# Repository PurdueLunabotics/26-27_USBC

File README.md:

# USBC board

Makes a stable USB-C voltage signal out of a DC input.

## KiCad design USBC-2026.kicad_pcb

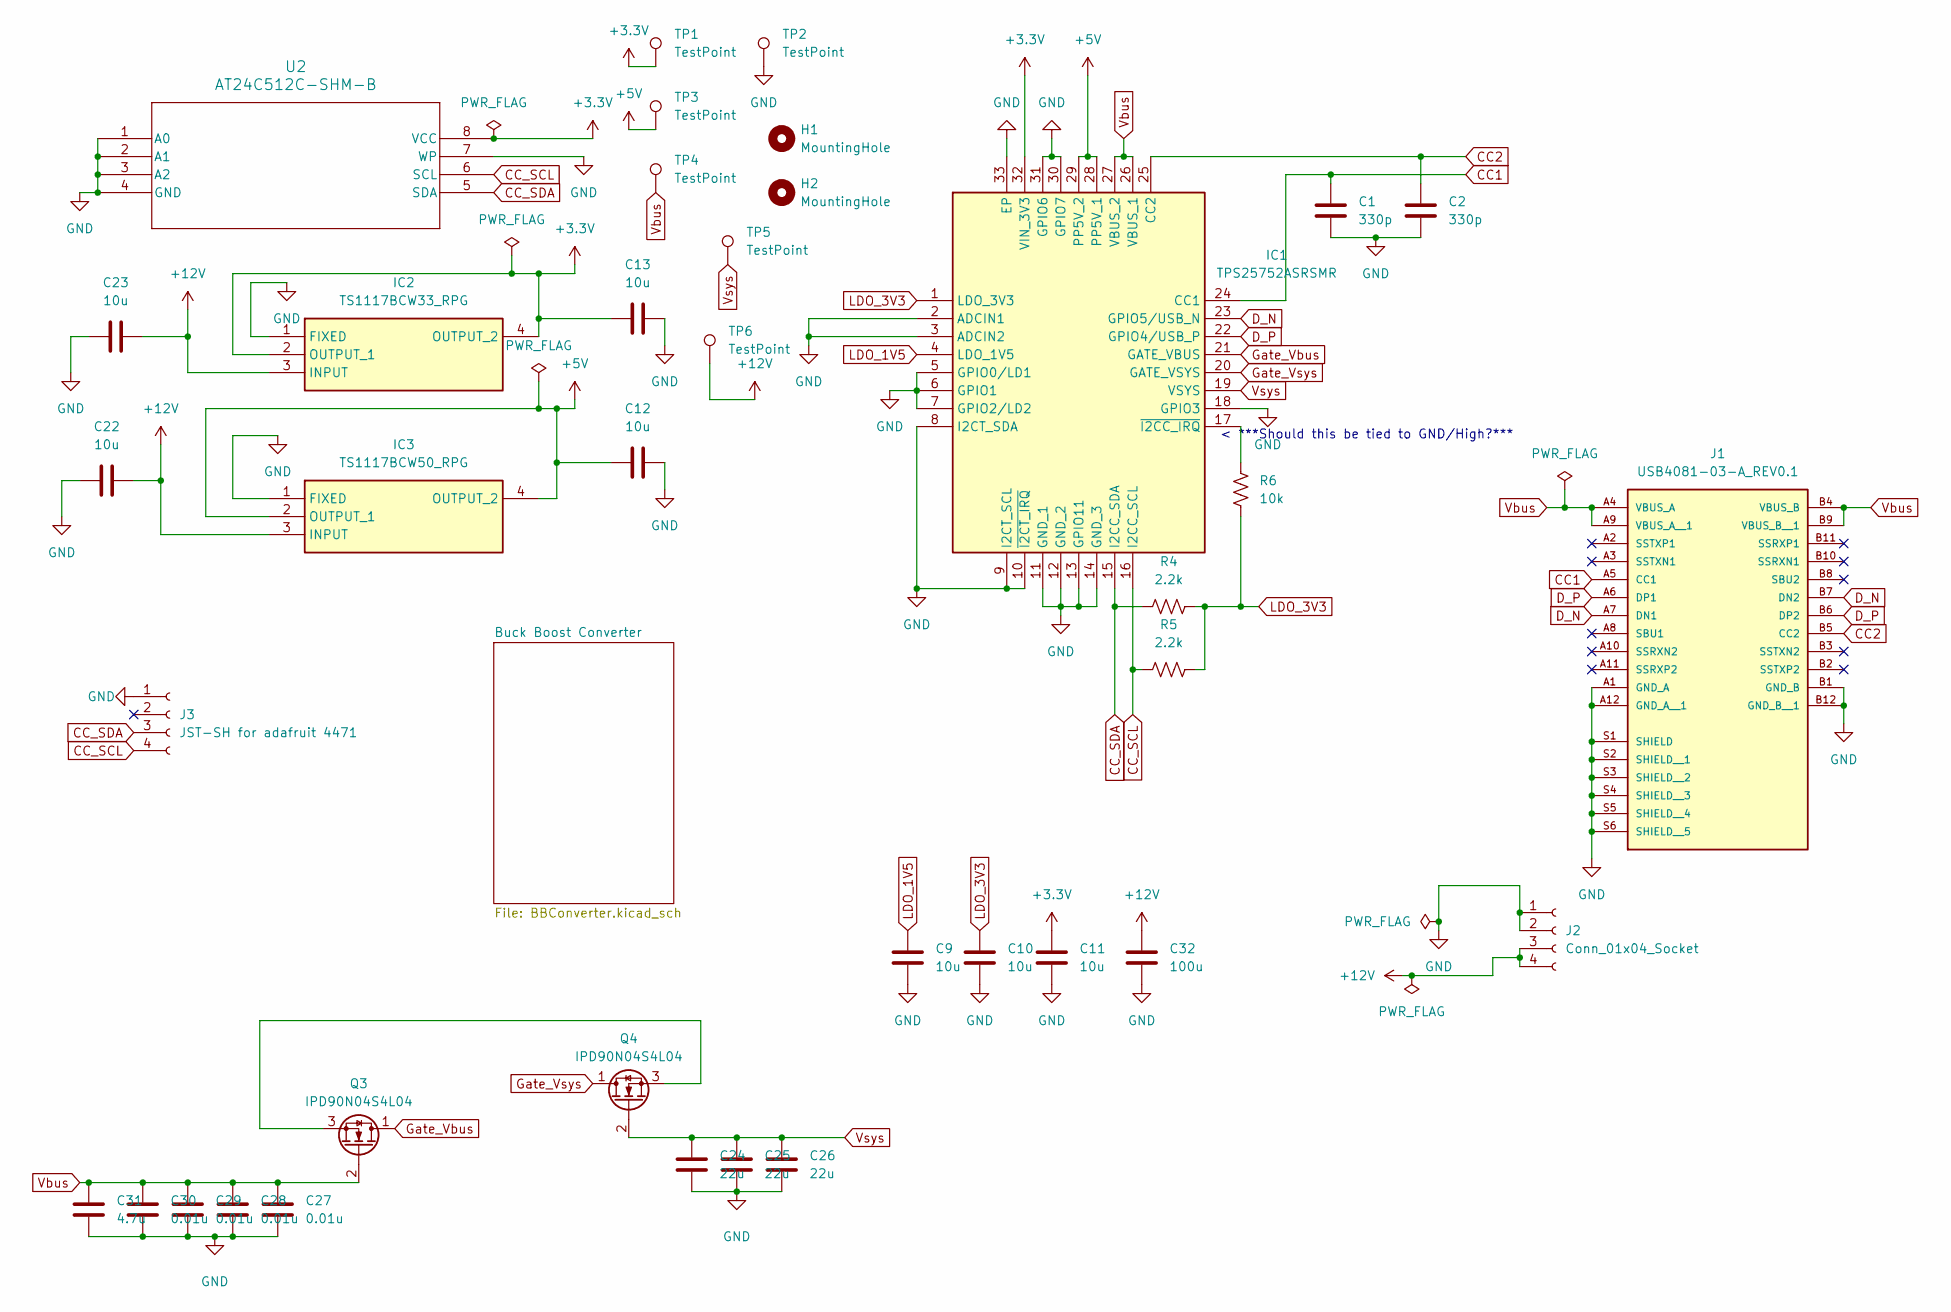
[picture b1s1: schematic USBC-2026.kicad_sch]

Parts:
C1, C2: 330p; C_0402_1005Metric
C9, C10, C11, C12, C13, C22, C23: 10u; C_0603_1608Metric
C24, C25, C26: 22u; C_1210_3225Metric
C27, C28, C29, C30: 0.01u; C_0402_1005Metric
C31: 4.7u; C_0603_1608Metric
C32: 100u; CP_Radial_D8.0mm_P3.50mm
H1, H2: MountingHole; MountingHole_2.2mm_M2_DIN965_Pad_TopBottom
IC1: TPS25752ASRSMR; QFN40P400X400X100-33N-D; Manufacturer_Part_Number TPS25752ASRSMR
IC2: TS1117BCW33_RPG; SOT-223; Mouser Part Number 821-TS1117BCW33RPG
IC3: TS1117BCW50_RPG; SOT-223; Mouser Part Number 821-TS1117BCW50RPG
J1: USB4081-03-A_REV0.1; GCT_USB4081-03-A_REV0.1; MPN USB4081-03-A
J2: Conn_01x04_Socket; CONN2_2604-1102_WAG
J3: JST-SH for adafruit 4471; JST_SH_BM04B-SRSS-TB_1x04-1MP_P1.00mm_Vertical
Q3, Q4: IPD90N04S4L04; TO-252-2
R4, R5: 2.2k; R_0402_1005Metric
R6: 10k; R_0402_1005Metric
TP1, TP2, TP3, TP4, TP5, TP6: TestPoint; TestPoint_Pad_D1.0mm
U2: AT24C512C-SHM-B; SOIC-8_3.9x4.9mm_P1.27mm

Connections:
+3.3V: C11.1, C13.1, IC1.32 (VIN_3V3), IC2.2 (OUTPUT_1), IC2.4 (OUTPUT_2), TP1.1 (1_1), U2.8 (VCC)
+5V: C12.1, IC1.28 (PP5V_1), IC1.29 (PP5V_2), IC3.2 (OUTPUT_1), IC3.4 (OUTPUT_2), TP3.1 (1_1)
+12V: C22.2, C23.2, C32.1, IC2.3 (INPUT), IC3.3 (INPUT), J2.3, J2.4, TP6.1 (1_1); also elsewhere on the board
CC1: C1.1, IC1.24 (CC1), J1.A5 (CC1)
CC2: C2.1, IC1.25 (CC2), J1.B5 (CC2)
CC_SCL: IC1.16 (I2CC_SCL), J3.4, R5.1, U2.6 (SCL); also elsewhere on the board
CC_SDA: IC1.15 (I2CC_SDA), J3.3, R4.1, U2.5 (SDA); also elsewhere on the board
D_N: IC1.23 (GPIO5/USB_N), J1.A7 (DN1), J1.B7 (DN2)
D_P: IC1.22 (GPIO4/USB_P), J1.A6 (DP1), J1.B6 (DP2)
GND: C1.2, C2.2, C9.1, C10.1, C11.2, C12.2, C13.2, C22.1, C23.1, C24.1, C25.1, C26.1, C27.1, C28.1, C29.1, C30.1, C31.1, C32.2, IC1.2 (ADCIN1), IC1.3 (ADCIN2), IC1.5 (GPIO0/LD1), IC1.6 (GPIO1), IC1.7 (GPIO2/LD2), IC1.8 (I2CT_SDA), IC1.9 (I2CT_SCL), IC1.10 (~I2CT_IRQ), IC1.11 (GND_1), IC1.12 (GND_2), IC1.13 (GPIO11), IC1.14 (GND_3), IC1.18 (GPIO3), IC1.30 (GPIO7), IC1.31 (GPIO6), IC1.33 (EP), IC2.1 (FIXED), IC3.1 (FIXED), J1.A1 (GND_A), J1.A12 (GND_A__1), J1.B1 (GND_B), J1.B12 (GND_B__1), J1.S1 (SHIELD), J1.S2 (SHIELD__1), J1.S3 (SHIELD__2), J1.S4 (SHIELD__3), J1.S5 (SHIELD__4), J1.S6 (SHIELD__5), J2.1, J2.2, J3.1, TP2.1 (1_1), U2.1 (A0), U2.2 (A1), U2.3 (A2), U2.4 (GND), U2.7 (WP); also elsewhere on the board
Gate_Vbus: IC1.21 (GATE_VBUS), Q3.1 (D)
Gate_Vsys: IC1.20 (GATE_VSYS), Q4.1 (D)
LDO_1V5: C9.2, IC1.4 (LDO_1V5)
LDO_3V3: C10.2, IC1.1 (LDO_3V3), R4.2, R5.2, R6.1
unnamed: IC1.17 (~I2CC_IRQ), R6.2
unnamed: Q3.3 (S), Q4.3 (S)
Vbus: C27.2, C28.2, C29.2, C30.2, C31.2, IC1.26 (VBUS_1), IC1.27 (VBUS_2), J1.A4 (VBUS_A), J1.A9 (VBUS_A__1), J1.B4 (VBUS_B), J1.B9 (VBUS_B__1), Q3.2 (G), TP4.1 (1_1)
Vsys: C24.2, C25.2, C26.2, IC1.19 (VSYS), Q4.2 (G), TP5.1 (1_1); also elsewhere on the board

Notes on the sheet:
< ***Should this be tied to GND/High?***

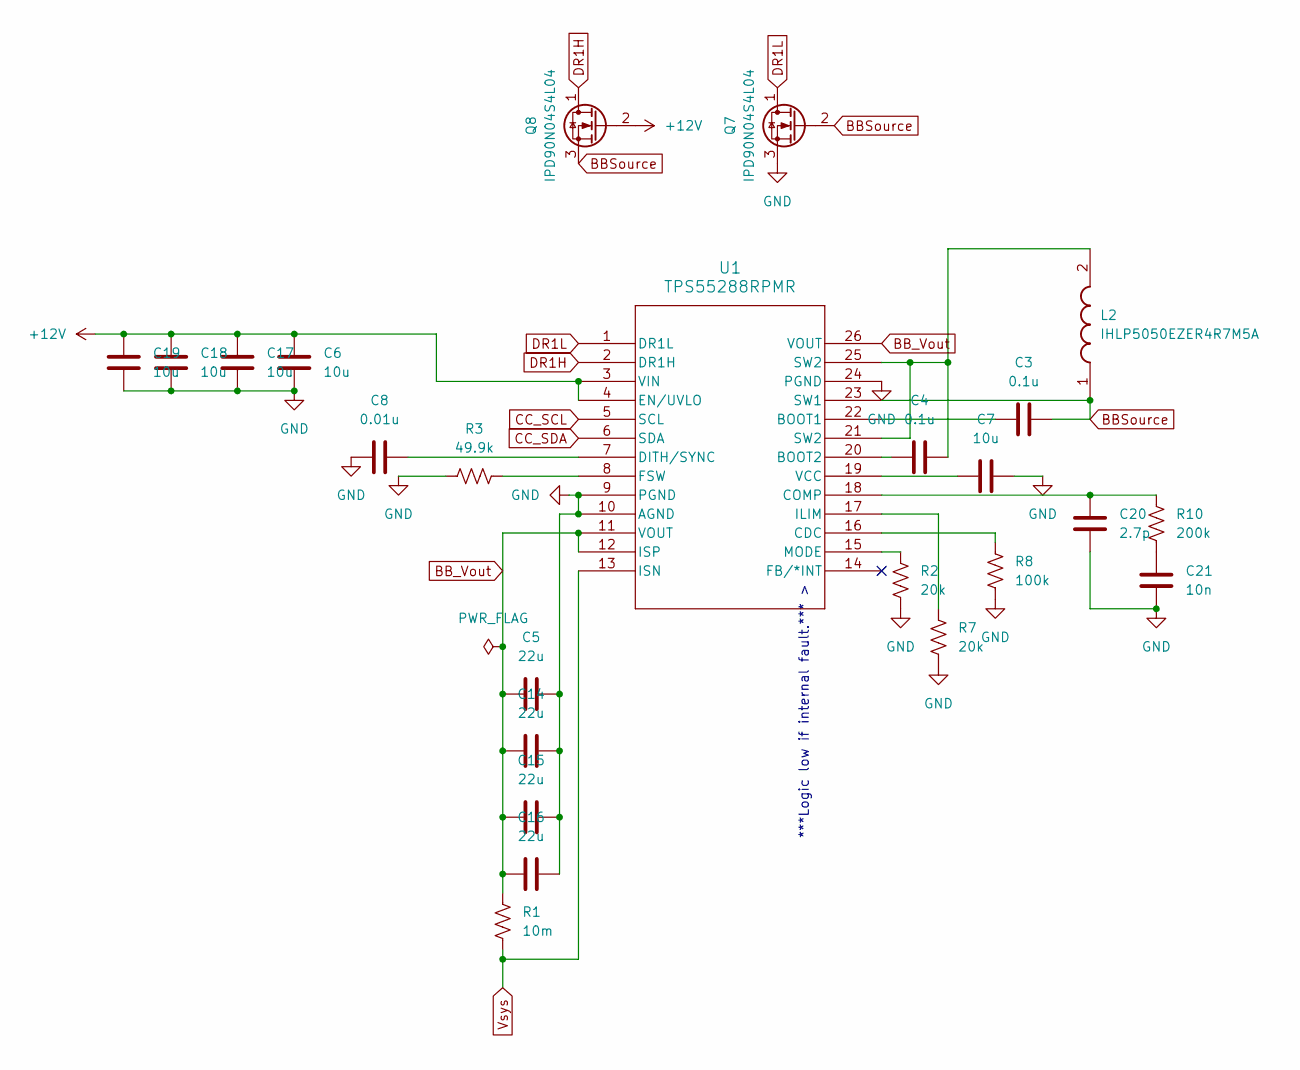
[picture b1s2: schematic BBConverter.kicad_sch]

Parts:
C3, C4: 0.1u; C_0402_1005Metric
C5, C14, C15, C16: 22u; C_1210_3225Metric
C6, C7, C17, C18, C19: 10u; C_0603_1608Metric
C8: 0.01u; C_0402_1005Metric
C20: 2.7p; C_0402_1005Metric
C21: 10n; C_0402_1005Metric
L2: IHLP5050EZER4R7M5A; L_Vishay_IHLP-5050-smaller-pad-width; Manufacturer_Part_Number IHLP5050EZER4R7M5A
Q7, Q8: IPD90N04S4L04; TO-252-2
R1: 10m; R_0603_1608Metric
R2, R7: 20k; R_0402_1005Metric
R3: 49.9k; R_0402_1005Metric
R8: 100k; R_0402_1005Metric
R10: 200k; R_0402_1005Metric
U1: TPS55288RPMR; VQFN-HR26_RPM_TEX

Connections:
+12V: C6.1, C17.1, C18.1, C19.1, Q8.2 (G), U1.3 (VIN), U1.4 (EN/UVLO); also elsewhere on the board
BBSource: C3.2, L2.1, Q7.2 (G), Q8.3 (S), U1.23 (SW1)
BB_Vout: C5.1, C14.1, C15.1, C16.1, R1.2, U1.11 (VOUT), U1.12 (ISP), U1.26 (VOUT)
CC_SCL: U1.5 (SCL); also elsewhere on the board
CC_SDA: U1.6 (SDA); also elsewhere on the board
DR1H: Q8.1 (D), U1.2 (DR1H)
DR1L: Q7.1 (D), U1.1 (DR1L)
GND: C5.2, C6.2, C7.2, C8.2, C14.2, C15.2, C16.2, C17.2, C18.2, C19.2, C20.1, C21.1, Q7.3 (S), R2.1, R3.2, R7.1, R8.1, U1.9 (PGND), U1.10 (AGND), U1.24 (PGND); also elsewhere on the board
unnamed: C4.2, L2.2, U1.21 (SW2), U1.25 (SW2)
unnamed: C21.2, R10.1
unnamed: C3.1, U1.22 (BOOT1)
unnamed: C4.1, U1.20 (BOOT2)
unnamed: R8.2, U1.16 (CDC)
unnamed: C20.2, R10.2, U1.18 (COMP)
unnamed: C8.1, U1.7 (DITH/SYNC)
unnamed: R3.1, U1.8 (FSW)
unnamed: R7.2, U1.17 (ILIM)
unnamed: R2.2, U1.15 (MODE)
unnamed: C7.1, U1.19 (VCC)
Vsys: R1.1, U1.13 (ISN); also elsewhere on the board

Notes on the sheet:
***Logic low if internal fault.*** >

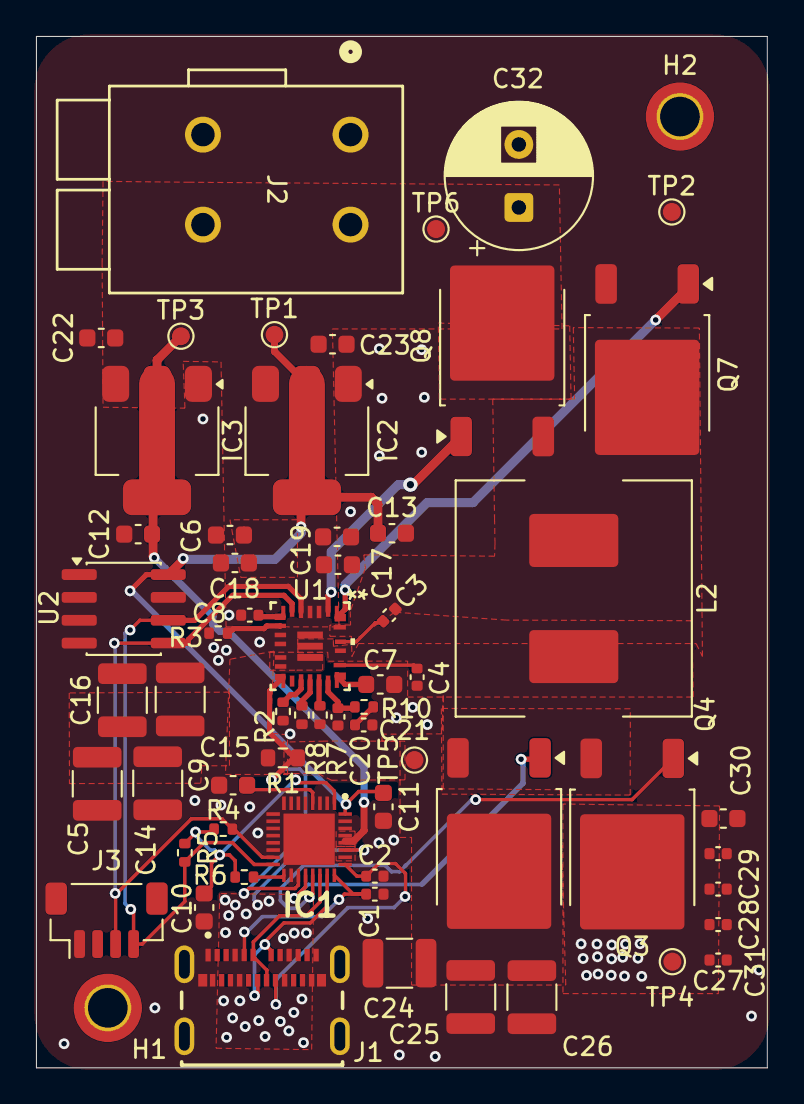
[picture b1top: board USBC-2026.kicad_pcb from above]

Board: 2 copper layers, 40.6 x 57.3 mm, 62 parts (0 on the bottom side), 33 nets.
